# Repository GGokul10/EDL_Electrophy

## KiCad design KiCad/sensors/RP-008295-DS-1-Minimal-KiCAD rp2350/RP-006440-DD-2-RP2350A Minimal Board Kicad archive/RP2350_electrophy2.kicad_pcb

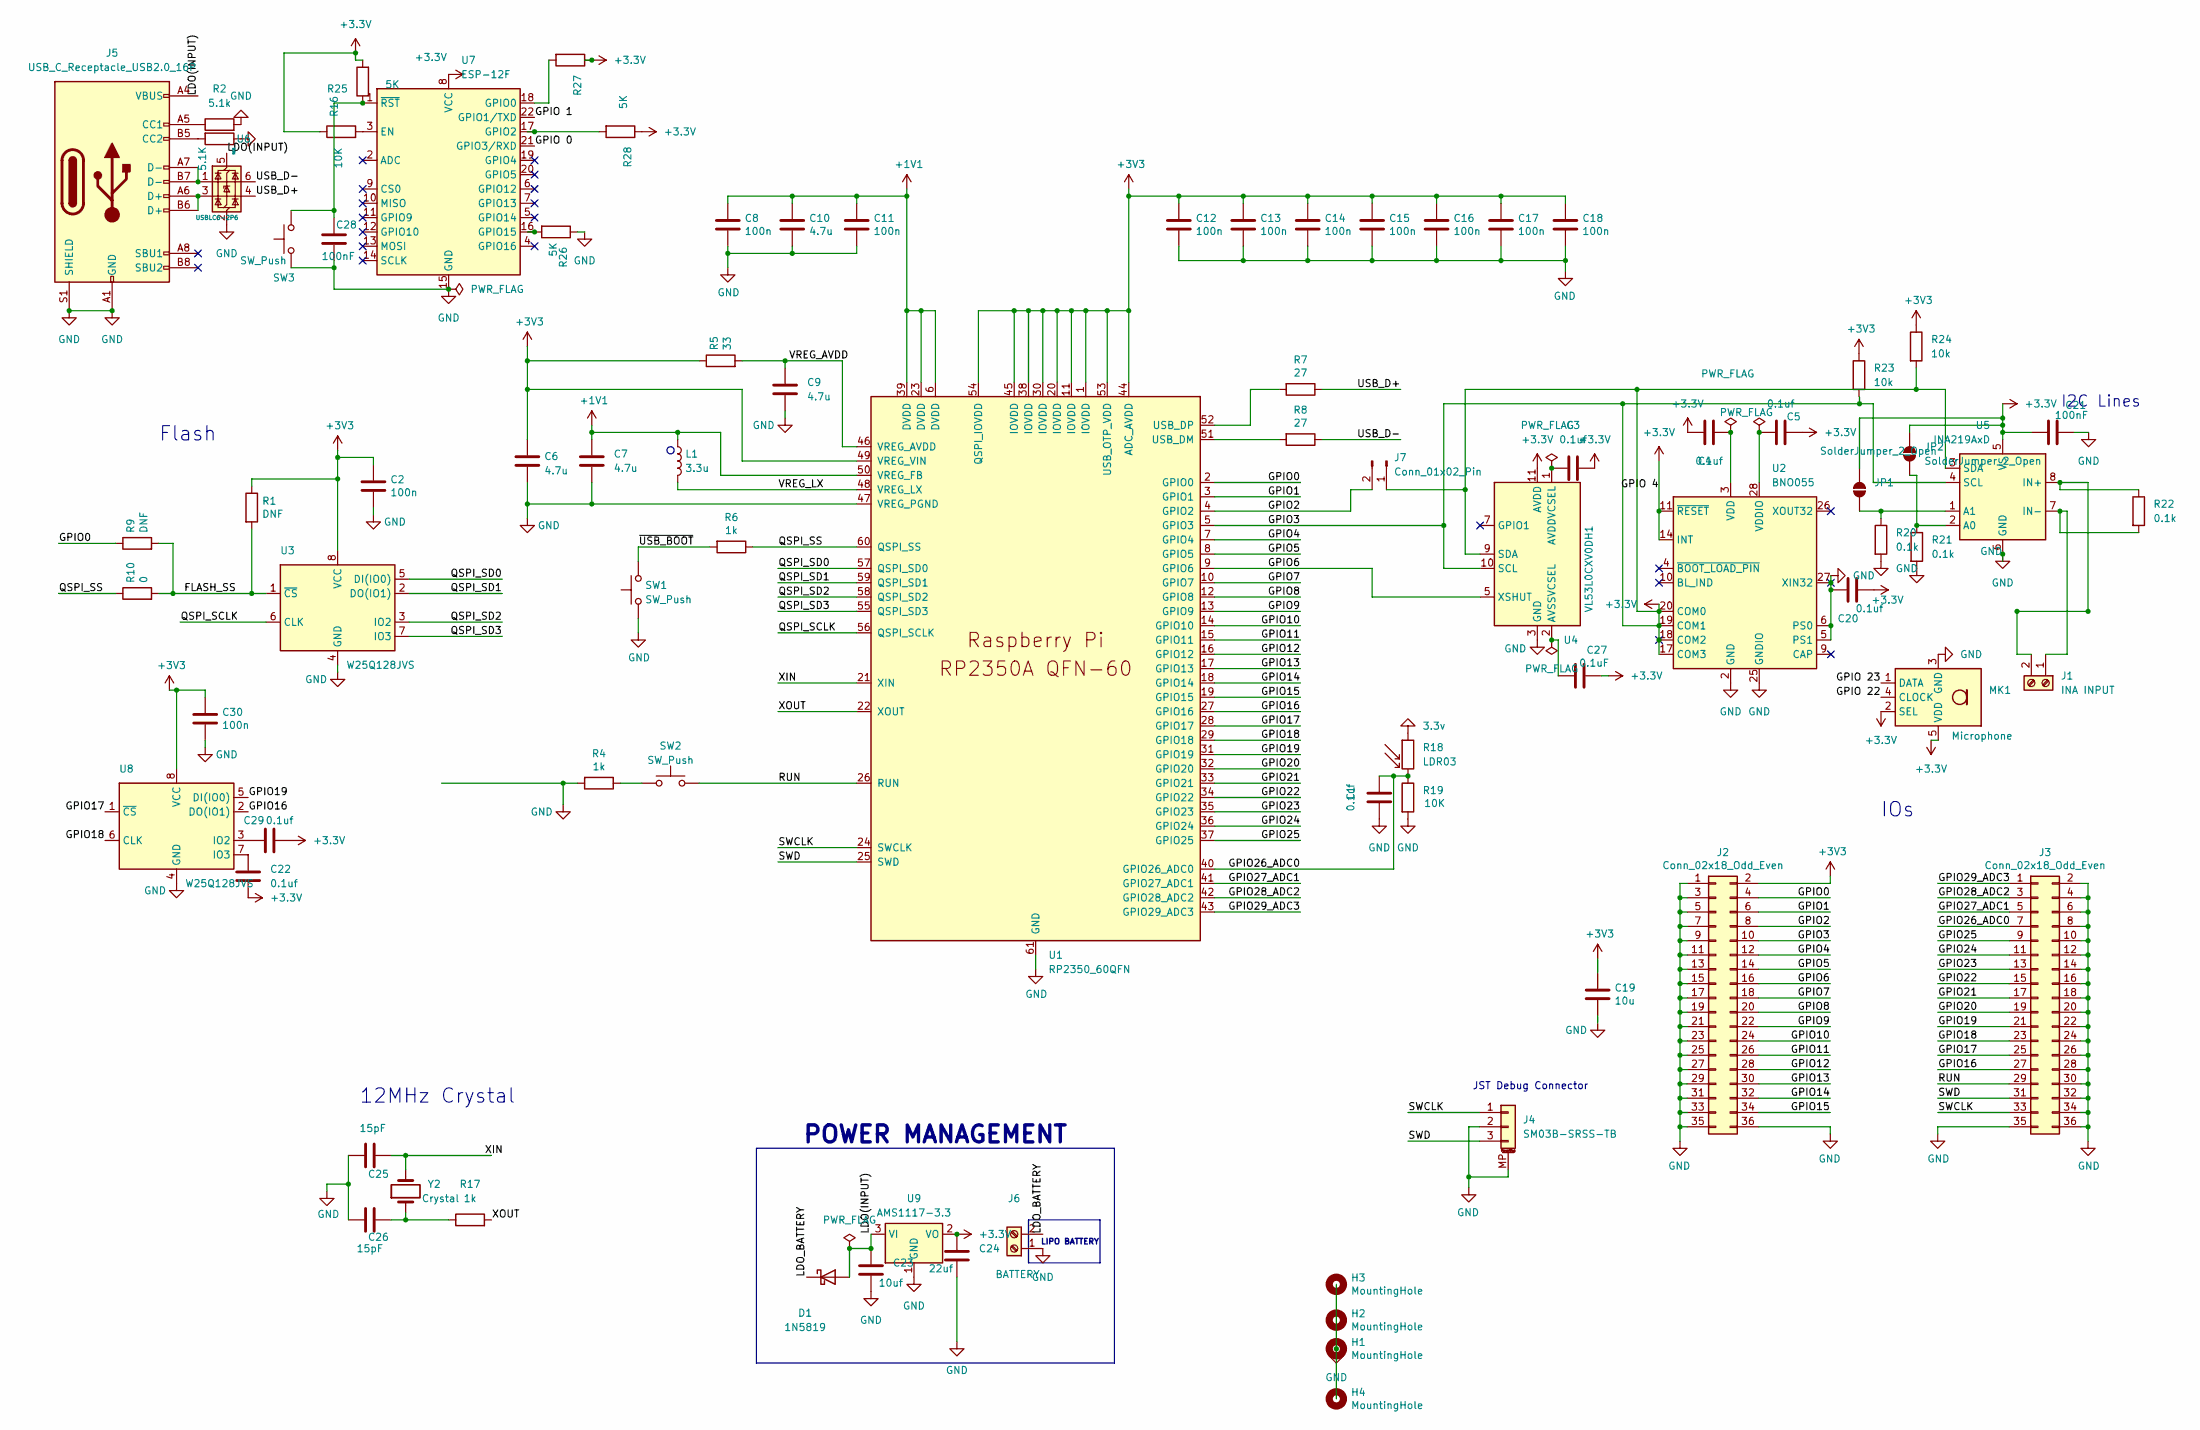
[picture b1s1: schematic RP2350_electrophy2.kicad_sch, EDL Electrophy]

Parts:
C1, C3, C4, C5, C20, C22, C29: 0.1uf; C_0603_1608Metric
C2, C8, C11, C12, C13, C14, C15, C16, C17, C18, C30: 100n; C_0603_1608Metric
C6, C7, C9, C10: 4.7u; C_0603_1608Metric
C19: 10u; C_0603_1608Metric
C21, C28: 100nF; C_0603_1608Metric
C23: 10uf; C_0603_1608Metric
C24: 22uf; C_0603_1608Metric
C25, C26: 15pF; C_0603_1608Metric
C27: 0.1uF; C_0603_1608Metric
D1: 1N5819; D_DO-41_SOD81_P10.16mm_Horizontal
H1, H2, H3, H4: MountingHole; MountingHole_2.7mm_M2.5
J1: INA INPUT; TerminalBlock_Phoenix_PT-1,5-2-5.0-H_1x02_P5.00mm_Horizontal
J2, J3: Conn_02x18_Odd_Even; PinHeader_2x18_P2.54mm_Vertical
J4: SM03B-SRSS-TB; JST_SH_SM03B-SRSS-TB_1x03-1MP_P1.00mm_Horizontal
J5: USB_C_Receptacle_USB2.0_16P; USB_C_Receptacle_GCT_USB4085
J6: BATTERY; JST_EH_B2B-EH-A_1x02_P2.50mm_Vertical
J7: Conn_01x02_Pin
JP1, JP2: SolderJumper_2_Open; SolderJumper-2_P1.3mm_Open_Pad1.0x1.5mm
L1: 3.3u; L_pol_2016
MK1: Microphone; Knowles_LGA-5_3.5x2.65mm
R1, R9: DNF; R_0603_1608Metric
R2: 5.1k; R_0603_1608Metric
R4, R6, R17: 1k; R_0603_1608Metric
R5: 33; R_0603_1608Metric
R7, R8: 27; R_0603_1608Metric
R10: 0; R_0603_1608Metric
R15: 5.1K; R_0603_1608Metric
R16, R19: 10K; R_0603_1608Metric
R18: LDR03; R_LDR_10x8.5mm_P7.6mm_Vertical
R20, R21, R22: 0.1k; R_0603_1608Metric
R23, R24: 10k; R_0603_1608Metric
R25, R26, R27, R28: 5K; R_0603_1608Metric
SW1, SW2, SW3: SW_Push; SW_SPST_TL3305A
U1: RP2350_60QFN; RP2350-QFN-60-1EP_7x7_P0.4mm_EP3.4x3.4mm_ThermalVias
U2: BNO055; LGA-28_5.2x3.8mm_P0.5mm
U3, U8: W25Q128JVS; SOIC-8_5.23x5.23mm_P1.27mm
U4: VL53L0CXV0DH1; ST_VL53L1x
U5: INA219AxD; SOIC-8_3.9x4.9mm_P1.27mm
U6: USBLC6-2P6; SOT-666
U7: ESP-12F; ESP-12E
U9: AMS1117-3.3; SOT-223-3_TabPin2
Y2: Crystal; Crystal_SMD_HC49-SD

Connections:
+1V1: C7.1, C8.1, C10.1, C11.1, L1.1, U1.6 (DVDD), U1.23 (DVDD), U1.39 (DVDD), U1.50 (VREG_FB)
+3.3V: C3.2, C4.2, C5.2, C20.1, C21.1, C22.1, C24.1, C27.2, C29.2, J2.10, J7.1, JP1.2 (B), JP2.2 (B), MK1.2 (SEL), MK1.5 (VDD), R16.1, R24.2, R25.2, R27.1, R28.1, U1.5 (GPIO3), U2.11 (~RESET), U2.14 (INT), U2.17 (COM3), U2.18 (COM2), U2.19 (COM1), U2.20 (COM0), U4.9 (SDA), U4.10 (SCL), U4.11 (AVDD), U5.3 (SDA), U5.4 (SCL), U5.5 (VS), U7.8 (VCC), U9.2 (VO)
+3V3: C2.1, C6.1, C12.1, C13.1, C14.1, C15.1, C16.1, C17.1, C18.1, C19.1, C30.1, J2.2, R1.1, R5.1, R23.1, R24.1, U1.1 (IOVDD), U1.11 (IOVDD), U1.20 (IOVDD), U1.30 (IOVDD), U1.38 (IOVDD), U1.44 (ADC_AVDD), U1.45 (IOVDD), U1.49 (VREG_VIN), U1.53 (USB_OTP_VDD), U1.54 (QSPI_IOVDD), U3.8 (VCC), U8.8 (VCC)
/FLASH_SS: R1.2, R9.2, R10.2, U3.1 (~CS)
/GPIO0: J2.4, R9.1, U1.2 (GPIO0)
/GPIO1: J2.6, U1.3 (GPIO1)
/GPIO2: J2.8, J7.2, U1.4 (GPIO2)
/GPIO4: J2.12, U1.7 (GPIO4)
/GPIO5: J2.14, U1.8 (GPIO5)
/GPIO6: J2.16, U1.9 (GPIO6), U4.5 (XSHUT)
/GPIO7: J2.18, U1.10 (GPIO7)
/GPIO8: J2.20, U1.12 (GPIO8)
/GPIO9: J2.22, U1.13 (GPIO9)
/GPIO10: J2.24, U1.14 (GPIO10)
/GPIO11: J2.26, U1.15 (GPIO11)
/GPIO12: J2.28, U1.16 (GPIO12)
/GPIO13: J2.30, U1.17 (GPIO13)
/GPIO14: J2.32, U1.18 (GPIO14)
/GPIO15: J2.34, U1.19 (GPIO15)
/GPIO16: J3.27, U1.27 (GPIO16), U8.2 (DO(IO1))
/GPIO17: J3.25, U1.28 (GPIO17), U8.1 (~CS)
/GPIO18: J3.23, U1.29 (GPIO18), U8.6 (CLK)
/GPIO19: J3.21, U1.31 (GPIO19), U8.5 (DI(IO0))
/GPIO20: J3.19, U1.32 (GPIO20)
/GPIO21: J3.17, U1.33 (GPIO21)
/GPIO22: J3.15, U1.34 (GPIO22)
/GPIO23: J3.13, U1.35 (GPIO23)
/GPIO24: J3.11, U1.36 (GPIO24)
/GPIO25: J3.9, U1.37 (GPIO25)
/GPIO26_ADC0: C1.2, J3.7, R18.2, R19.1, U1.40 (GPIO26_ADC0)
/GPIO27_ADC1: J3.5, U1.41 (GPIO27_ADC1)
/GPIO28_ADC2: J3.3, U1.42 (GPIO28_ADC2)
/GPIO29_ADC3: J3.1, U1.43 (GPIO29_ADC3)
/GPIO 0: U7.21 (GPIO3/RXD)
/GPIO 1: U7.22 (GPIO1/TXD)
/GPIO 22: MK1.4 (CLOCK)
/GPIO 23: MK1.1 (DATA)
/LDO(INPUT): C23.1, D1.2 (A), J5.A4 (VBUS), J5.A9 (VBUS), J5.B4 (VBUS), J5.B9 (VBUS), U6.5 (VBUS), U9.3 (VI)
/LDO_BATTERY: D1.1 (K), J6.2
/QSPI_SCLK: U1.56 (QSPI_SCLK), U3.6 (CLK)
/QSPI_SD0: U1.57 (QSPI_SD0), U3.5 (DI(IO0))
/QSPI_SD1: U1.59 (QSPI_SD1), U3.2 (DO(IO1))
/QSPI_SD2: U1.58 (QSPI_SD2), U3.3 (IO2)
/QSPI_SD3: U1.55 (QSPI_SD3), U3.7 (IO3)
/QSPI_SS: R6.1, R10.1, U1.60 (QSPI_SS)
/RUN: J3.29, SW2.2, U1.26 (RUN)
/SWCLK: J3.33, J4.1, U1.24 (SWCLK)
/SWD: J3.31, J4.3, U1.25 (SWD)
/USB_D+: R7.1, U6.4 (I/O2)
/USB_D-: R8.1, U6.6 (I/O1)
/VREG_AVDD: C9.1, R5.2, U1.46 (VREG_AVDD)
/VREG_LX: L1.2, U1.48 (VREG_LX)
/XIN: C25.1, U1.21 (XIN), Y2.2
/XOUT: R17.2, U1.22 (XOUT)
/~USB_BOOT: R6.2, SW1.2
unnamed: C22.2, U8.7 (IO3)
unnamed: C26.1, R17.1, Y2.1
unnamed: C29.1, U8.3 (IO2)
unnamed: J1.1, R22.2, U5.7 (IN-)
unnamed: J1.2, R22.1, U5.8 (IN+)
unnamed: J5.A5 (CC1), R2.1
unnamed: J5.B5 (CC2), R15.2
unnamed: J5.A6 (D+), J5.B6 (D+), U6.3 (I/O2)
unnamed: J5.A7 (D-), J5.B7 (D-), U6.1 (I/O1)
unnamed: JP1.1 (A), R20.1, U5.1 (A1)
unnamed: JP2.1 (A), R21.1, U5.2 (A0)
unnamed: R4.1, SW2.1
unnamed: R8.2, U1.51 (USB_DM)
unnamed: R7.2, U1.52 (USB_DP)
unnamed: C4.1, U2.3 (VDD)
unnamed: C5.1, U2.28 (VDDIO)
unnamed: C3.1, U4.1 (AVDDVCSEL)
unnamed: C27.1, U4.2 (AVSSVCSEL)
unnamed: R16.2, U7.3 (EN)
unnamed: R27.2, U7.18 (GPIO0)
unnamed: R28.2, U7.17 (GPIO2)
unnamed: R26.2, U7.16 (GPIO15)
unnamed: C28.1, R25.1, SW3.2, U7.1 (~RST)

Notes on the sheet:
JST Debug Connector
IOs
LIPO BATTERY
I2C Lines
Flash
POWER MANAGEMENT
12MHz Crystal

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
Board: 2 copper layers, 76 parts (0 on the bottom side), 68 nets, no tracks yet.

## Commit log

2026-03-13 datastorage
2026-03-13 Revert "sss"
    This reverts commit 86fe283a7360912680efa0920751a16ecdecdf7f.
2026-03-14 Revert "SSA"
    This reverts commit dae8b1a79ed248bb7f18b4eb6a44a2ca605acb61.
